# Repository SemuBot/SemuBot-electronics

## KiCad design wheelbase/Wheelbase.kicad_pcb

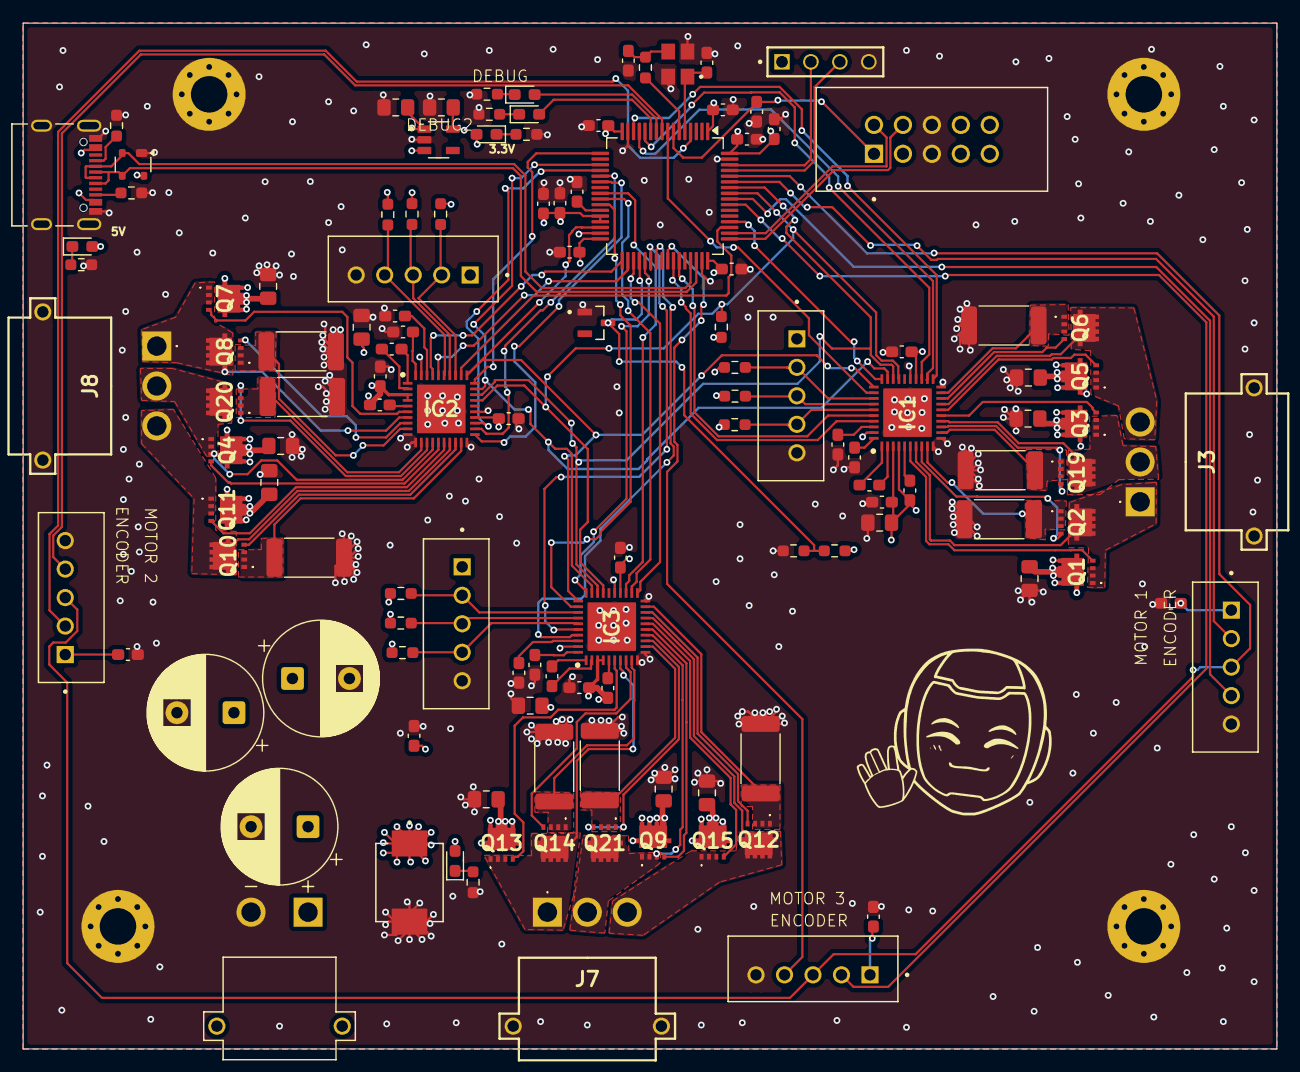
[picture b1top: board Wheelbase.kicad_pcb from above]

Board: 4 copper layers, 110.0 x 90.0 mm, 129 parts (0 on the bottom side), 117 nets.

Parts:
C1, C4: 10uF; C_0805_2012Metric_Pad1.18x1.45mm_HandSolder
C3, C13, C14, C15, C16, C34, C44, C45, C46, C47, C48, C49, C53: 100nF; C_0603_1608Metric_Pad1.08x0.95mm_HandSolder
C5, C6, C17, C18, C23, C24: 0.1uF; C_0603_1608Metric_Pad1.08x0.95mm_HandSolder
C7, C19, C25: 10uF; C_0603_1608Metric_Pad1.08x0.95mm_HandSolder
C8, C20, C26: 47nF; C_0603_1608Metric_Pad1.08x0.95mm_HandSolder
C9, C21, C27, C28, C29, C30: 1uF; C_0603_1608Metric_Pad1.08x0.95mm_HandSolder
C10, C11: 10pF; C_0603_1608Metric_Pad1.08x0.95mm_HandSolder
C12: 4.7uF; C_0603_1608Metric_Pad1.08x0.95mm_HandSolder
C31, C32, C33: 22uF; C_0805_2012Metric_Pad1.18x1.45mm_HandSolder
C35, C36, C37, C38, C39, C40, C41, C42, C43: 1uF 50V X7R; C_0805_2012Metric_Pad1.18x1.45mm_HandSolder
C50, C51, C52: 470uF 5mm 63V Polymer; CP_Radial_D10.0mm_P5.00mm
D1: green; LED_0603_1608Metric_Pad1.05x0.95mm_HandSolder
D2, D7, D8, D9: red; LED_0603_1608Metric_Pad1.05x0.95mm_HandSolder
D3: PRTR5V0U2X; SOT-143
D4: BZX84C3V3; SOT95P240X115-3N
D5: SMCJ33A; DIOM6859X262N
H1: MH1; MountingHole_3.2mm_M3_Pad_Via
H2: MH2; MountingHole_3.2mm_M3_Pad_Via
H3: MH3; MountingHole_3.2mm_M3_Pad_Via
H4: MH4; MountingHole_3.2mm_M3_Pad_Via
IC1, IC2, IC3: DRV8353FSRTAR; QFN50P600X600X80-41N-D
J1: 10155435-00011LF; AMPHENOL_10155435-00011LF
J3, J7, J8: MR30PW-M; MR30PWM
J4, J5, J6, J10, J11, J12: B5B-XH-A_LF__SN_; JST_B5B-XH-A_LF__SN_
J9: DS1013-10SSIB1; CONNFLY_DS1013-10SSIB1
J13: MTSW-104-09-L-S-400; SAMTEC_MTSW-104-09-L-S-400
J14: XT30PW-M; AMASS_XT30PW-M
Q1, Q2, Q3, Q4, Q5, Q6, Q7, Q8, Q9, Q10, Q11, Q12, Q13, Q14, Q15, Q19, Q20, Q21: AONR62818; AON7262E
R1, R2: 5.1K; R_0603_1608Metric_Pad0.98x0.95mm_HandSolder
R5: 47; R_0603_1608Metric_Pad0.98x0.95mm_HandSolder
R6, R18, R19, R20, R25, R45: 3.3K; R_0603_1608Metric_Pad0.98x0.95mm_HandSolder
R9, R10, R11, R12, R13, R14, R15, R16, R17: 10mΩ; R_2512_6332Metric_Pad1.40x3.35mm_HandSolder
R26: 91k; R_0603_1608Metric_Pad0.98x0.95mm_HandSolder
R27: 10k; R_0603_1608Metric_Pad0.98x0.95mm_HandSolder
R29, R30, R31, R32, R33, R34, R35, R37, R38: 1.5K; R_0603_1608Metric_Pad0.98x0.95mm_HandSolder
U1: STM32G474RET6; LQFP-64_10x10mm_P0.5mm
U5: RT9013-33GB; SOT94P279X129-5N
Y2: X322516MLB4SI; OSC_X322516MLB4SI

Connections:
+3.3V: C4.2, C6.1, C12.1, C13.1, C14.1, C15.1, C16.1, C18.1, C24.1, C44.1, C45.1, C46.1, D8.2 (A), IC1.24 (VREF), IC2.24 (VREF), IC3.24 (VREF), J9.7, J9.8, J13.01, U1.1 (VBAT), U1.16 (VDD), U1.28 (VREF+), U1.29 (VDDA), U1.32 (VDD), U1.48 (VDD), U1.64 (VDD), U5.5 (VOUT)
+5V: C1.2, C47.1, C48.1, C49.1, D3.4 (VCC), D9.2 (A), J1.A4_B9 (VBUS), J1.B4_A9 (VBUS), J4.1, J5.1, J6.1, J10.1, J11.1, J12.1, R29.2, R30.2, R31.2, R32.2, R33.2, R34.2, R35.2, R37.2, R38.2, R45.2, U5.1 (VIN), U5.3 (EN)
+24V: C5.1, C9.2, C17.1, C21.2, C23.1, C27.2, C31.2, C32.2, C33.2, C35.1, C36.1, C37.1, C38.1, C39.1, C40.1, C41.1, C42.1, C43.1, C50.1, C51.1, C52.1, C53.1, D5.C, D7.2 (A), IC1.3 (VM), IC1.4 (VDRAIN), IC2.3 (VM), IC2.4 (VDRAIN), IC3.3 (VM), IC3.4 (VDRAIN), J14.P, Q1.5 (D), Q1.6 (D), Q1.7 (D), Q1.8 (D), Q1.9 (D), Q1.10 (D), Q1.11 (D), Q3.5 (D), Q3.6 (D), Q3.7 (D), Q3.8 (D), Q3.9 (D), Q3.10 (D), Q3.11 (D), Q4.5 (D), Q4.6 (D), Q4.7 (D), Q4.8 (D), Q4.9 (D), Q4.10 (D), Q4.11 (D), Q5.5 (D), Q5.6 (D), Q5.7 (D), Q5.8 (D), Q5.9 (D), Q5.10 (D), Q5.11 (D), Q7.5 (D), Q7.6 (D), Q7.7 (D), Q7.8 (D), Q7.9 (D), Q7.10 (D), Q7.11 (D), Q9.5 (D), Q9.6 (D), Q9.7 (D), Q9.8 (D), Q9.9 (D), Q9.10 (D), Q9.11 (D), Q11.5 (D), Q11.6 (D), Q11.7 (D), Q11.8 (D), Q11.9 (D), Q11.10 (D), Q11.11 (D), Q13.5 (D), Q13.6 (D), Q13.7 (D), Q13.8 (D), Q13.9 (D), Q13.10 (D), Q13.11 (D), Q15.5 (D), Q15.6 (D), Q15.7 (D), Q15.8 (D), Q15.9 (D), Q15.10 (D), Q15.11 (D), R26.1
/ADC1_IN1: IC1.23 (SOA), U1.12 (PA0)
/ADC1_IN2: IC1.22 (SOB), U1.13 (PA1)
/ADC1_IN3: IC1.21 (SOC), U1.14 (PA2)
/ADC2_IN3: IC2.23 (SOA), U1.20 (PA6)
/ADC2_IN4: IC2.22 (SOB), U1.21 (PA7)
/ADC2_IN5: IC2.21 (SOC), U1.22 (PC4)
/ADC3_IN1: IC3.22 (SOB), U1.25 (PB1)
/ADC3_IN5: IC3.21 (SOC), U1.35 (PB13)
/ADC3_IN12: IC3.23 (SOA), U1.24 (PB0)
/ADC4_IN3: D4.3, R26.2, R27.1, U1.36 (PB14)
/CAN_RX: J13.03, U1.61 (PB8)
/CAN_TX: J13.02, U1.62 (PB9)
/CS_ENC_1: J10.4, U1.56 (PB3)
/CS_ENC_2: J11.4, U1.9 (PC1)
/CS_ENC_3: J12.4, U1.41 (PC9)
/D+: D3.3 (I/O2), J1.A6 (DP1), J1.B6 (DP2), U1.46 (PA12)
/D-: D3.2 (I/O1), J1.A7 (DN1), J1.B7 (DN2), U1.45 (PA11)
/ENABLE: IC1.31 (ENABLE), IC2.31 (ENABLE), IC3.31 (ENABLE), U1.30 (PB10)
/MOTOR1_DIR: IC1.36 (INHC), U1.43 (PA9)
/MOTOR1_PWM: IC1.32 (INHA), U1.8 (PC0)
/MOTOR2_DIR: IC2.36 (INHC), U1.34 (PB12)
/MOTOR2_PWM: IC2.32 (INHA), U1.51 (PA15)
/MOTOR3_DIR: IC3.36 (INHC), U1.38 (PC6)
/MOTOR3_PWM: IC3.32 (INHA), U1.26 (PB2)
/Motor_1/GHA: IC1.6 (GHA), Q1.4 (G)
/Motor_1/GHB: IC1.15 (GHB), Q3.4 (G)
/Motor_1/GHC: IC1.16 (GHC), Q5.4 (G)
/Motor_1/GLA: IC1.8 (GLA), Q2.4 (G)
/Motor_1/GLB: IC1.13 (GLB), Q19.4 (G)
/Motor_1/GLC: IC1.18 (GLC), Q6.4 (G)
/Motor_1/HAL_1: IC1.33 (INLA), J4.2, R29.1
/Motor_1/HAL_2: IC1.34 (INHB), J4.3, R32.1
/Motor_1/HAL_3: IC1.35 (INLB), J4.4, R35.1
/Motor_1/SHA: IC1.7 (SHA), J3.1, Q1.1 (S), Q1.2 (S), Q1.3 (S), Q2.5 (D), Q2.6 (D), Q2.7 (D), Q2.8 (D), Q2.9 (D), Q2.10 (D), Q2.11 (D)
/Motor_1/SHB: IC1.14 (SHB), J3.2, Q3.1 (S), Q3.2 (S), Q3.3 (S), Q19.5 (D), Q19.6 (D), Q19.7 (D), Q19.8 (D), Q19.9 (D), Q19.10 (D), Q19.11 (D)
/Motor_1/SHC: IC1.17 (SHC), J3.3, Q5.1 (S), Q5.2 (S), Q5.3 (S), Q6.5 (D), Q6.6 (D), Q6.7 (D), Q6.8 (D), Q6.9 (D), Q6.10 (D), Q6.11 (D)
/Motor_1/SPA: IC1.9 (SPA), Q2.1 (S), Q2.2 (S), Q2.3 (S), R9.2
/Motor_1/SPB: IC1.12 (SPB), Q19.1 (S), Q19.2 (S), Q19.3 (S), R15.2
/Motor_1/SPC: IC1.19 (SPC), Q6.1 (S), Q6.2 (S), Q6.3 (S), R12.2
/Motor_2/GHA: IC2.6 (GHA), Q7.4 (G)
/Motor_2/GHB: IC2.15 (GHB), Q4.4 (G)
/Motor_2/GHC: IC2.16 (GHC), Q11.4 (G)
/Motor_2/GLA: IC2.8 (GLA), Q8.4 (G)
/Motor_2/GLB: IC2.13 (GLB), Q20.4 (G)
/Motor_2/GLC: IC2.18 (GLC), Q10.4 (G)
/Motor_2/HAL_1: IC2.33 (INLA), J5.2, R30.1
/Motor_2/HAL_2: IC2.34 (INHB), J5.3, R33.1
/Motor_2/HAL_3: IC2.35 (INLB), J5.4, R37.1
/Motor_2/SHA: IC2.7 (SHA), J8.1, Q7.1 (S), Q7.2 (S), Q7.3 (S), Q8.5 (D), Q8.6 (D), Q8.7 (D), Q8.8 (D), Q8.9 (D), Q8.10 (D), Q8.11 (D)
/Motor_2/SHB: IC2.14 (SHB), J8.2, Q4.1 (S), Q4.2 (S), Q4.3 (S), Q20.5 (D), Q20.6 (D), Q20.7 (D), Q20.8 (D), Q20.9 (D), Q20.10 (D), Q20.11 (D)
/Motor_2/SHC: IC2.17 (SHC), J8.3, Q10.5 (D), Q10.6 (D), Q10.7 (D), Q10.8 (D), Q10.9 (D), Q10.10 (D), Q10.11 (D), Q11.1 (S), Q11.2 (S), Q11.3 (S)
/Motor_2/SPA: IC2.9 (SPA), Q8.1 (S), Q8.2 (S), Q8.3 (S), R10.2
/Motor_2/SPB: IC2.12 (SPB), Q20.1 (S), Q20.2 (S), Q20.3 (S), R16.2
/Motor_2/SPC: IC2.19 (SPC), Q10.1 (S), Q10.2 (S), Q10.3 (S), R13.2
/Motor_3/GHA: IC3.6 (GHA), Q13.4 (G)
/Motor_3/GHB: IC3.15 (GHB), Q9.4 (G)
/Motor_3/GHC: IC3.16 (GHC), Q15.4 (G)
/Motor_3/GLA: IC3.8 (GLA), Q14.4 (G)
/Motor_3/GLB: IC3.13 (GLB), Q21.4 (G)
/Motor_3/GLC: IC3.18 (GLC), Q12.4 (G)
/Motor_3/HAL_1: IC3.33 (INLA), J6.2, R31.1
/Motor_3/HAL_2: IC3.34 (INHB), J6.3, R34.1
/Motor_3/HAL_3: IC3.35 (INLB), J6.4, R38.1
/Motor_3/SHA: IC3.7 (SHA), J7.1, Q13.1 (S), Q13.2 (S), Q13.3 (S), Q14.5 (D), Q14.6 (D), Q14.7 (D), Q14.8 (D), Q14.9 (D), Q14.10 (D), Q14.11 (D)
/Motor_3/SHB: IC3.14 (SHB), J7.2, Q9.1 (S), Q9.2 (S), Q9.3 (S), Q21.5 (D), Q21.6 (D), Q21.7 (D), Q21.8 (D), Q21.9 (D), Q21.10 (D), Q21.11 (D)
/Motor_3/SHC: IC3.17 (SHC), J7.3, Q12.5 (D), Q12.6 (D), Q12.7 (D), Q12.8 (D), Q12.9 (D), Q12.10 (D), Q12.11 (D), Q15.1 (S), Q15.2 (S), Q15.3 (S)
/Motor_3/SPA: IC3.9 (SPA), Q14.1 (S), Q14.2 (S), Q14.3 (S), R11.2
/Motor_3/SPB: IC3.12 (SPB), Q21.1 (S), Q21.2 (S), Q21.3 (S), R17.2
/Motor_3/SPC: IC3.19 (SPC), Q12.1 (S), Q12.2 (S), Q12.3 (S), R14.2
/NRST: C3.2, J9.1, U1.7 (PG10)
/OSC_IN: C11.1, U1.5 (PF0), Y2.1
/OSC_OUT: R5.1, U1.6 (PF1)
/SPI_CLK: IC1.29 (SCLK), IC2.29 (SCLK), IC3.29 (SCLK), U1.19 (PA5)
/SPI_DATA: IC1.27 (SDO), IC2.27 (SDO), IC3.27 (SDO), R45.1, U1.57 (PB4)
/SPI_MOSI: IC1.28 (SDI), IC2.28 (SDI), IC3.28 (SDI), U1.58 (PB5)
/SSI_CLK: J10.3, J11.3, J12.3, U1.60 (PB7)
/SWCLK: J9.2, U1.50 (PA14)
/SWDIO: J9.4, U1.49 (PA13)
/enc_1_data: J10.2, U1.59 (PB6)
/enc_2_data: J11.2, U1.4 (PC15)
/enc_3_data: J12.2, U1.55 (PD2)
/motor1_Cs: IC1.30 (NSCS), U1.52 (PC10)
/motor1_nBRAKE: IC1.37 (INLC), U1.42 (PA8)
/motor2_Cs: IC2.30 (NSCS), U1.17 (PA3)
/motor2_nBRAKE: IC2.37 (INLC), U1.33 (PB11)
/motor3_Cs: IC3.30 (NSCS), U1.37 (PB15)
/motor3_nBRAKE: IC3.37 (INLC), U1.39 (PC7)
GND: C1.1, C3.1, C4.1, C5.2, C6.2, C7.2, C10.1, C11.2, C12.2, C13.2, C14.2, C15.2, C16.2, C17.2, C18.2, C19.2, C23.2, C24.2, C25.2, C28.1, C29.1, C30.1, C31.1, C32.1, C33.1, C34.2, C35.2, C36.2, C37.2, C38.2, C39.2, C40.2, C41.2, C42.2, C43.2, C44.2, C45.2, C46.2, C47.2, C48.2, C49.2, C50.2, C51.2, C52.2, C53.2, D3.1 (GND), D4.1, D5.A, H1.1 (1_1), H2.1 (1_1), H3.1 (1_1), H4.1 (1_1), IC1.10 (SNA), IC1.11 (SNB), IC1.20 (SNC), IC1.25 (AGND), IC1.39 (GND_1), IC1.41 (GND_2), IC2.10 (SNA), IC2.11 (SNB), IC2.20 (SNC), IC2.25 (AGND), IC2.39 (GND_1), IC2.41 (GND_2), IC3.10 (SNA), IC3.11 (SNB), IC3.20 (SNC), IC3.25 (AGND), IC3.39 (GND_1), IC3.41 (GND_2), J1.A1_B12 (GND), J1.B1_A12 (GND), J1.SH1 (SHIELD), J1.SH2 (SHIELD), J1.SH3 (SHIELD), J1.SH4 (SHIELD), J3.4 (MH1), J3.5 (MH2), J4.5, J5.5, J6.5, J7.4 (MH1), J7.5 (MH2), J8.4 (MH1), J8.5 (MH2), J9.5, J9.6, J10.5, J11.5, J12.5, J13.04, J14.N, R1.1, R2.1, R6.2, R9.1, R10.1, R11.1, R12.1, R13.1, R14.1, R15.1, R16.1, R17.1, R18.2, R19.2, R20.2, R25.2, R27.2, U1.15 (VSS), U1.31 (VSS), U1.47 (VSS), U1.63 (VSS), U5.2 (GND), Y2.2, Y2.4
unnamed: C10.2, R5.2, Y2.3
unnamed: D1.2 (A), U1.11 (PC3)
unnamed: D1.1 (K), R25.1
unnamed: D2.2 (A), U1.10 (PC2)
unnamed: D2.1 (K), R6.1
unnamed: D7.1 (K), R18.1
unnamed: D8.1 (K), R19.1
unnamed: D9.1 (K), R20.1
unnamed: C8.1, IC1.2 (CPH)
unnamed: C8.2, IC1.1 (CPL)
unnamed: C7.1, IC1.38 (DVDD)
unnamed: C9.1, IC1.5 (VCP)
unnamed: C28.2, IC1.40 (VGLS)
unnamed: C20.1, IC2.2 (CPH)
unnamed: C20.2, IC2.1 (CPL)
unnamed: C19.1, IC2.38 (DVDD)
unnamed: C21.1, IC2.5 (VCP)
unnamed: C29.2, IC2.40 (VGLS)
unnamed: C26.1, IC3.2 (CPH)
unnamed: C26.2, IC3.1 (CPL)
unnamed: C25.1, IC3.38 (DVDD)
unnamed: C27.1, IC3.5 (VCP)
unnamed: C30.2, IC3.40 (VGLS)
unnamed: J1.A5 (CC1), R1.2
unnamed: J1.B5 (CC2), R2.2
unnamed: C34.1, U1.27 (VSSA)

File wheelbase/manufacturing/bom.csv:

Designator,Footprint,Quantity,Value,LCSC Part #
"C1, C4",0805,2,10uF,
"C10, C11",0603,2,10pF,
C12,0603,1,4.7uF,
"C13, C14, C15, C16, C3, C34, C44, C45, C46, C47, C48, C49, C53",0603,13,100nF,
"C17, C18, C23, C24, C5, C6",0603,6,0.1uF,
"C19, C25, C7",0603,3,10uF,
"C20, C26, C8",0603,3,47nF,
"C21, C27, C28, C29, C30, C9",0603,6,1uF,
"C31, C32, C33",0805,3,22uF,
"C35, C36, C37, C38, C39, C40, C41, C42, C43",0805,9,1uF 50V X7R,
"C50, C51, C52",CP_Radial_D10.0mm_P5.00mm,3,470uF 5mm 63V Polymer,
D1,0603,1,green,
"D2, D7, D8, D9",0603,4,red,
D3,SOT-143,1,PRTR5V0U2X,
D4,SOT95P240X115-3N,1,BZX84C3V3,
D5,DIOM6859X262N,1,SMCJ33A,
"IC1, IC2, IC3",QFN50P600X600X80-41N-D,3,DRV8353FSRTAR,
J1,AMPHENOL_10155435-00011LF,1,10155435-00011LF,
"J10, J11, J12, J4, J5, J6",JST_B5B-XH-A_LF__SN_,6,B5B-XH-A_LF__SN_,
J13,SAMTEC_MTSW-104-09-L-S-400,1,MTSW-104-09-L-S-400,
J14,AMASS_XT30PW-M,1,XT30PW-M,
"J3, J7, J8",MR30PWM,3,MR30PW-M,
J9,CONNFLY_DS1013-10SSIB1,1,DS1013-10SSIB1,
"Q1, Q10, Q11, Q12, Q13, Q14, Q15, Q19, Q2, Q20, Q21, Q3, Q4, Q5, Q6, Q7, Q8, Q9",AON7262E,18,AONR62818,
"R1, R2",0603,2,5.1K,
"R10, R11, R12, R13, R14, R15, R16, R17, R9",2512,9,10mΩ,
"R18, R19, R20, R25, R45, R6",0603,6,3.3K,
R26,0603,1,91k,
R27,0603,1,10k,
"R29, R30, R31, R32, R33, R34, R35, R37, R38",0603,9,1.5K,
R5,0603,1,47,
U1,LQFP-64_10x10mm_P0.5mm,1,STM32G474RET6,
U5,SOT94P279X129-5N,1,RT9013-33GB,
Y2,OSC_X322516MLB4SI,1,X322516MLB4SI,

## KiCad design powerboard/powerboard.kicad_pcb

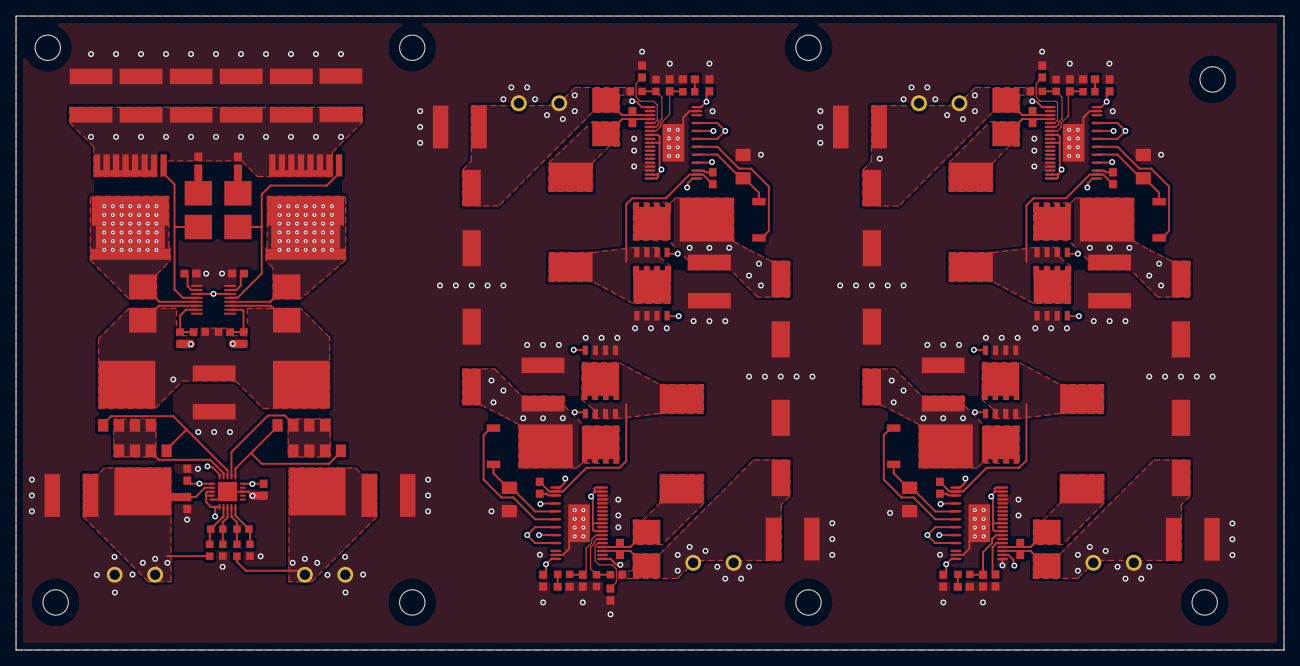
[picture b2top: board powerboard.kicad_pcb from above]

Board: 4 copper layers, 160.0 x 80.0 mm, 122 parts (0 on the bottom side), 75 nets.

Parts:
C1, C3, C10, C13, C19, C22, C26, C31: CAPAE10083X105M
C2, C4, C20, C24: FP-GRM31C-0_2-e0_3_0_8-IPC_A
C5, C6, C7, C8, C9, C11, C12, C14, C15, C16, C17, C18, C21, C23, C25, C27, C28, C29, C30, C32, C33, C34, C35, C36, C37, C41, C42, C43, C44, C45, C46: CAPC1608X10N
C38, C39, C40, C47, C48, C49, C50, C51, C52, C53, C54, C55, C56, C57, C58, C59, C60: CAPC5750X31N
J1, J2, J3, J4, J5, J6: 1711725-Footprint-1
L1, L2, L3, L4: INDP134126X50N
Q1, Q3, Q7, Q9: INF-PG-TO252-3-11_A_L
Q2, Q4, Q5, Q6, Q8, Q10, Q11, Q12: INF-PG-TDSON-8-1_V
Q13, Q14, Q16, Q17: DPAK200P800X170-5N
Q15, Q18: INF-PG-HSOF-8-1_V
R1, R3, R7, R9, R15, R16, R23, R24: RESC6432X09N
R2, R4, R5, R6, R8, R10, R11, R12, R13, R14, R17, R18, R19, R20, R21, R22, R25, R26, R27, R28: RESC1608X06N
U1, U2, U3, U4: TSSOP50P640X120_HS-39N
U5: FP-MS-16-05-08-1669-IPC_B
U6: ADI-UF-20_V

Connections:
5V: C13.1, C16.1, C58.1, J6.2, R3.2, U2.4, U2.6
12V: C10.1, C15.1, C57.1, J5.2, R1.2, R5.2, U1.4, U1.32, U2.32, U3.32, U4.32
19V: C31.1, C34.1, C60.1, J4.2, R9.2, R12.1, U4.4
24V: C26.1, C33.1, C59.1, J3.2, R7.2, R11.2, U3.4
BATTERY: C38.2, C45.1, J2.2, Q13.D, R26.2, U6.16
CHARGER: C40.2, C43.1, J1.1, Q16.D, R20.2, U6.17
CURRENT_LIMITER: C39.2, Q14.D, Q17.D, R15.1, R17.2, R21.1, R23.1, U5.3, U5.14, U6.15
GND: C1.2, C2.1, C3.2, C4.1, C5.2, C7.1, C8.2, C10.2, C11.1, C12.1, C13.2, C14.1, C17.1, C18.1, C19.2, C20.1, C21.2, C22.2, C24.1, C25.1, C26.2, C27.2, C28.1, C30.1, C31.2, C32.1, C35.1, C36.1, C38.1, C39.1, C40.1, C41.2, C42.1, C43.2, C45.2, C46.2, C47.1, C48.1, C49.1, C50.1, C51.1, C52.1, C53.1, C54.1, C55.1, C56.1, C57.2, C58.2, C59.2, C60.2, J1.2, J2.1, J3.1, J4.1, J5.1, J6.1, Q5.S, Q6.S, Q11.S, Q12.S, R6.1, R13.1, R14.1, R18.1, R19.1, R25.1, R28.1, U1.1, U1.9, U1.12, U1.15, U1.16, U1.17, U1.37, U1.39, U2.1, U2.9, U2.12, U2.15, U2.16, U2.17, U2.37, U2.39, U3.1, U3.9, U3.12, U3.15, U3.16, U3.17, U3.37, U3.39, U4.1, U4.9, U4.12, U4.15, U4.16, U4.17, U4.37, U4.39, U5.8, U5.9, U6.8, U6.20, U6.21
NetC2_2: C2.2, Q1.3, U1.26
NetC4_2: C4.2, Q3.3, U2.26
NetC5_1: C5.1, U1.5
NetC6_1: C6.1, L1.1, Q2.S, Q5.D, U1.21
NetC6_2: C6.2, U1.22
NetC7_2: C7.2, R2.1
NetC8_1: C8.1, U2.5
NetC9_1: C9.1, L2.1, Q4.S, Q6.D, U2.21
NetC9_2: C9.2, U2.22
NetC11_2: C11.2, R4.1
NetC12_2: C12.2, R2.2, U1.7
NetC14_2: C14.2, R4.2, U2.7
NetC15_2: C15.2, L1.2, R1.1, U1.3
NetC16_2: C16.2, L2.2, R3.1, U2.3
NetC17_2: C17.2, U1.8, U1.10, U1.18, U1.19, U1.38
NetC18_2: C18.2, U2.2, U2.8, U2.10, U2.18, U2.19, U2.38
NetC20_2: C20.2, Q7.3, U3.26
NetC21_1: C21.1, U3.5
NetC23_1: C23.1, L3.1, Q8.S, Q11.D, U3.21
NetC23_2: C23.2, U3.22
NetC24_2: C24.2, Q9.3, U4.26
NetC25_2: C25.2, R8.1
NetC27_1: C27.1, U4.5
NetC28_2: C28.2, R8.2, U3.7
NetC29_1: C29.1, L4.1, Q10.S, Q12.D, U4.21
NetC29_2: C29.2, U4.22
NetC30_2: C30.2, R10.1
NetC32_2: C32.2, R10.2, U4.7
NetC33_2: C33.2, L3.2, R7.1, U3.3
NetC34_2: C34.2, L4.2, R9.1, U4.3
NetC35_2: C35.2, U3.8, U3.10, U3.18, U3.19, U3.38
NetC36_2: C36.2, U4.8, U4.10, U4.18, U4.19, U4.38
NetC37_1: C37.1, R16.2
NetC41_1: C41.1, U5.7
NetC42_2: C42.2, U5.10
NetC44_1: C44.1, R24.2
NetC46_1: C46.1, U6.1, U6.10, U6.18, U6.19
NetQ1_1: Q1.1, U1.28
NetQ2_G: Q2.G, U1.20
NetQ3_1: Q3.1, U2.28
NetQ4_G: Q4.G, U2.20
NetQ5_G: Q5.G, U1.24
NetQ6_G: Q6.G, U2.24
NetQ7_1: Q7.1, U3.28
NetQ8_G: Q8.G, U3.20
NetQ9_1: Q9.1, U4.28
NetQ10_G: Q10.G, U4.20
NetQ11_G: Q11.G, U3.24
NetQ12_G: Q12.G, U4.24
NetQ13_G: Q13.G, Q14.G, U6.11
NetQ13_S: Q13.S, Q14.S, U6.12
NetQ15_D: Q15.D, R15.2, U5.4
NetQ15_G: Q15.G, R16.1, U5.5
NetQ16_G: Q16.G, Q17.G, U6.13
NetQ16_S: Q16.S, Q17.S, U6.14
NetQ18_D: Q18.D, R23.2, U5.13
NetQ18_G: Q18.G, R24.1, U5.12
NetR5_1: R5.1, R6.2, U1.6
NetR11_1: R11.1, R13.2, U3.6
NetR12_2: R12.2, R14.2, U4.6
NetR17_1: R17.1, R18.2, U5.2
NetR19_2: R19.2, R21.2, U5.15
NetR20_1: R20.1, R22.2, U6.2
NetR22_1: R22.1, R25.2, U6.3
NetR26_1: R26.1, R27.2, U6.4
NetR27_1: R27.1, R28.2, U6.5
PCB_PWR: C1.1, C3.1, C19.1, C22.1, C37.2, C44.2, C47.2, C48.2, C49.2, C50.2, C51.2, C52.2, C53.2, C54.2, C55.2, C56.2, Q1.2, Q2.D, Q3.2, Q4.D, Q7.2, Q8.D, Q9.2, Q10.D, Q15.S, Q18.S, U1.30, U1.34, U2.30, U2.34, U3.30, U3.34, U4.30, U4.34, U5.6, U5.11

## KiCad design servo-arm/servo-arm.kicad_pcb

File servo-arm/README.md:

# Kaur-thesis-2025-servo-arm
Each separate project folder contains a corresponding readme.
<br>
## Python UI
Instructions and code found in folder ```Servo-Controller-Python-UI```.<br>
Link to original repository: https://github.com/martinkaur/Servo-controller-python-lib.git
<br>
## Controller board firmware
Instructions and code found in folder ```Servo-Controller-Firmware```.<br>
Link to original repository: https://github.com/martinkaur/Servo-Arm-Driver.git
<br>
## Controller board Altium Designer project files
Files found in folder ```Servo-Controller-Altium-Designer-Project-Files```.<br>
Link to original repository: https://github.com/martinkaur/Servo-Arm-Controller-Design.git

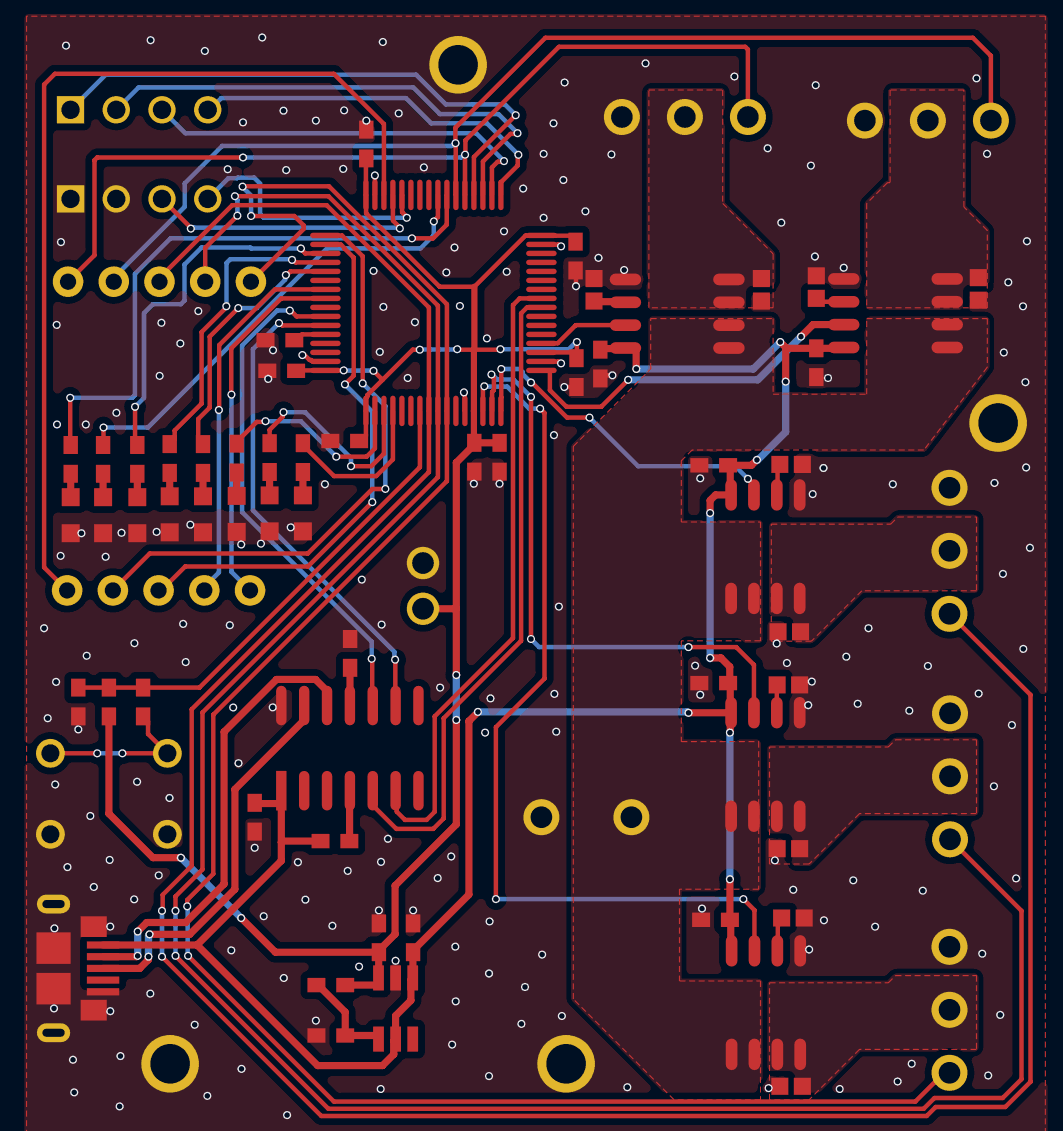
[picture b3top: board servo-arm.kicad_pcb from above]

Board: 2 copper layers, 70 parts (0 on the bottom side), 63 nets.

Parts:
C1, C2, C3, C4, C5, C6, C7, C8, C9, C10, C11, C14, C15, C16, C19, C22, C25: CAPC1608X08N
C12, C13, C17, C18, C20, C21, C23, C24, C26, C27: CAPC1608X90X40NL10T20
D1, D2, D3, D4, D5, D6, D7, D8: DIOM1608X11N
J1, J6: Header-2.54-ZL201-05G-Footprint-1
J2: 2_pin_f_2_54-Footprint-1
J3, J4: SMTC-MTLW-104-07-X-S-125
J5: USB3076-XX-X_revC
J7, J8, J10, J11, J12: 691103110003
J9: 5mmScrewTerminal-Footprint-1
R1, R2, R3, R4, R5, R6, R7, R8, R9, R10, R11, R12, R13, R14: RESC1608X04N
SW1: Button 6mm tht-Footprint-1
U1: LQFP50P1235X1235X165-64N
U2: FP-C04-065-SL-IPC_B
U3, U5, U6, U7, U8: SOIC127P600X175-8N
U4: SOT95P280X145-6N

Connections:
12V: J9.2, U3.1, U3.2, U5.1, U5.2, U6.1, U6.2, U7.1, U7.2, U8.1, U8.2
CAN_RX: J4.4, U1.44
CAN_TX: J4.3, U1.45
GND: C1.2, C2.1, C3.2, C4.2, C5.2, C6.2, C7.2, C8.2, C9.2, C10.2, C11.2, C12.1, C13.1, C14.1, C15.2, C16.2, C17.1, C18.1, C19.2, C20.1, C21.1, C22.2, C23.1, C24.1, C25.2, C26.1, C27.1, D1.1, D2.1, D3.1, D4.1, D5.1, D6.1, D7.1, D8.1, J2.2, J4.1, J4.2, J5.5, J5.S, J7.3, J8.3, J9.1, J10.3, J11.3, J12.3, R1.1, R14.2, SW1.2, U1.12, U1.18, U1.31, U1.47, U1.63, U2.14, U3.5, U4.2, U5.5, U6.5, U7.5, U8.5
I2C1_SCL: U1.58, U2.10
I2C1_SDA: U1.59, U2.9
JTDI: J1.3, U1.50
JTDO: J1.4, U1.55
JTRST: J1.5, U1.56
LED_DEBUG_1: R11.1, U1.39
LED_DEBUG_2: R10.1, U1.40
LED_DEBUG_3: R7.1, U1.51
LED_DEBUG_4: R6.1, U1.52
LED_DEBUG_5: R5.1, U1.53
LED_DEBUG_6: R4.1, U1.2
LED_DEBUG_7: R3.1, U1.3
LED_DEBUG_8: R2.1, U1.4
MCU_NRST: C2.2, R8.2, R9.1, U1.7
Motor1_PWM: J6.1, J7.1, U1.10
Motor1_Power: C13.2, J7.2, U3.3, U3.4
Motor2_PWM: J6.2, J8.1, U1.9
Motor2_Power: C18.2, J8.2, U5.3, U5.4
Motor3_PWM: J6.3, J10.1, U1.8
Motor3_Power: C21.2, J10.2, U6.3, U6.4
Motor4_PWM: J6.4, J11.1, U1.38
Motor4_Power: C24.2, J11.2, U7.3, U7.4
Motor5_PWM: J6.5, J12.1, U1.37
Motor5_Power: C27.2, J12.2, U8.3, U8.4
NetC5_1: C5.1, U2.11
NetC12_2: C12.2, U3.6
NetC17_2: C17.2, U5.6
NetC20_2: C20.2, U6.6
NetC23_2: C23.2, U7.6
NetC26_2: C26.2, U8.6
NetD1_2: D1.2, R2.2
NetD2_2: D2.2, R3.2
NetD3_2: D3.2, R4.2
NetD4_2: D4.2, R5.2
NetD5_2: D5.2, R6.2
NetD6_2: D6.2, R7.2
NetD7_2: D7.2, R10.2
NetD8_2: D8.2, R11.2
NetJ5_2: J5.2, U2.12
NetJ5_3: J5.3, U2.13
NetR1_2: R1.2, U1.60
NetR9_2: R9.2, SW1.1
NetR12_1: R12.1, U2.4
NetR13_2: R13.2, R14.1, U4.4
NetU1_14: U1.14, U3.7
NetU1_15: U1.15, U5.7
NetU1_16: U1.16, U6.7
NetU1_17: U1.17, U7.7
NetU1_20: U1.20, U8.7
SPI2_MISO: J3.2, U1.35
SPI2_MOSI: J3.1, U1.36
SPI2_NSS: J3.4, U1.33
SPI2_SCK: J3.3, U1.34
SWCLK-JTCK: J1.2, U1.49
SWDIO-JTMS: J1.1, U1.46
USART1_RX: U1.24, U2.5
USART1_TX: U1.25, U2.6
VDD_CAP_filter_1: C1.1, C3.1, C4.1, C7.1, C8.1, C9.1, C10.1, C15.1, J2.1, R8.1, R13.1, U1.1, U1.13, U1.19, U1.32, U1.48, U1.64, U4.3
VUSB (5V): C6.1, C11.1, C14.2, C16.1, C19.1, C22.1, C25.1, J5.1, R12.2, U2.1, U3.8, U4.1, U4.5, U5.8, U6.8, U7.8, U8.8

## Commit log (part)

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2026-01-28 Added SPI and CAN support
2026-01-28 Wheelbase development and repo cleanup
2026-02-02 Current sensing
2026-02-04 Gerber files
2026-02-04 Current sensing, + changing encoder pins
2026-03-06 Updated pdf
2026-03-23 Encoder fix
2026-03-23 Removed SPI version, kept HW version
2026-03-23 Removed HW version, added it into a branch
2026-03-23 .gitignore
2026-03-23 Git cleanup
2026-03-23 Updated mosfet symbols and organization
2026-03-30 Fixing schematics
2026-04-14 Re organizing, adding .pdf
